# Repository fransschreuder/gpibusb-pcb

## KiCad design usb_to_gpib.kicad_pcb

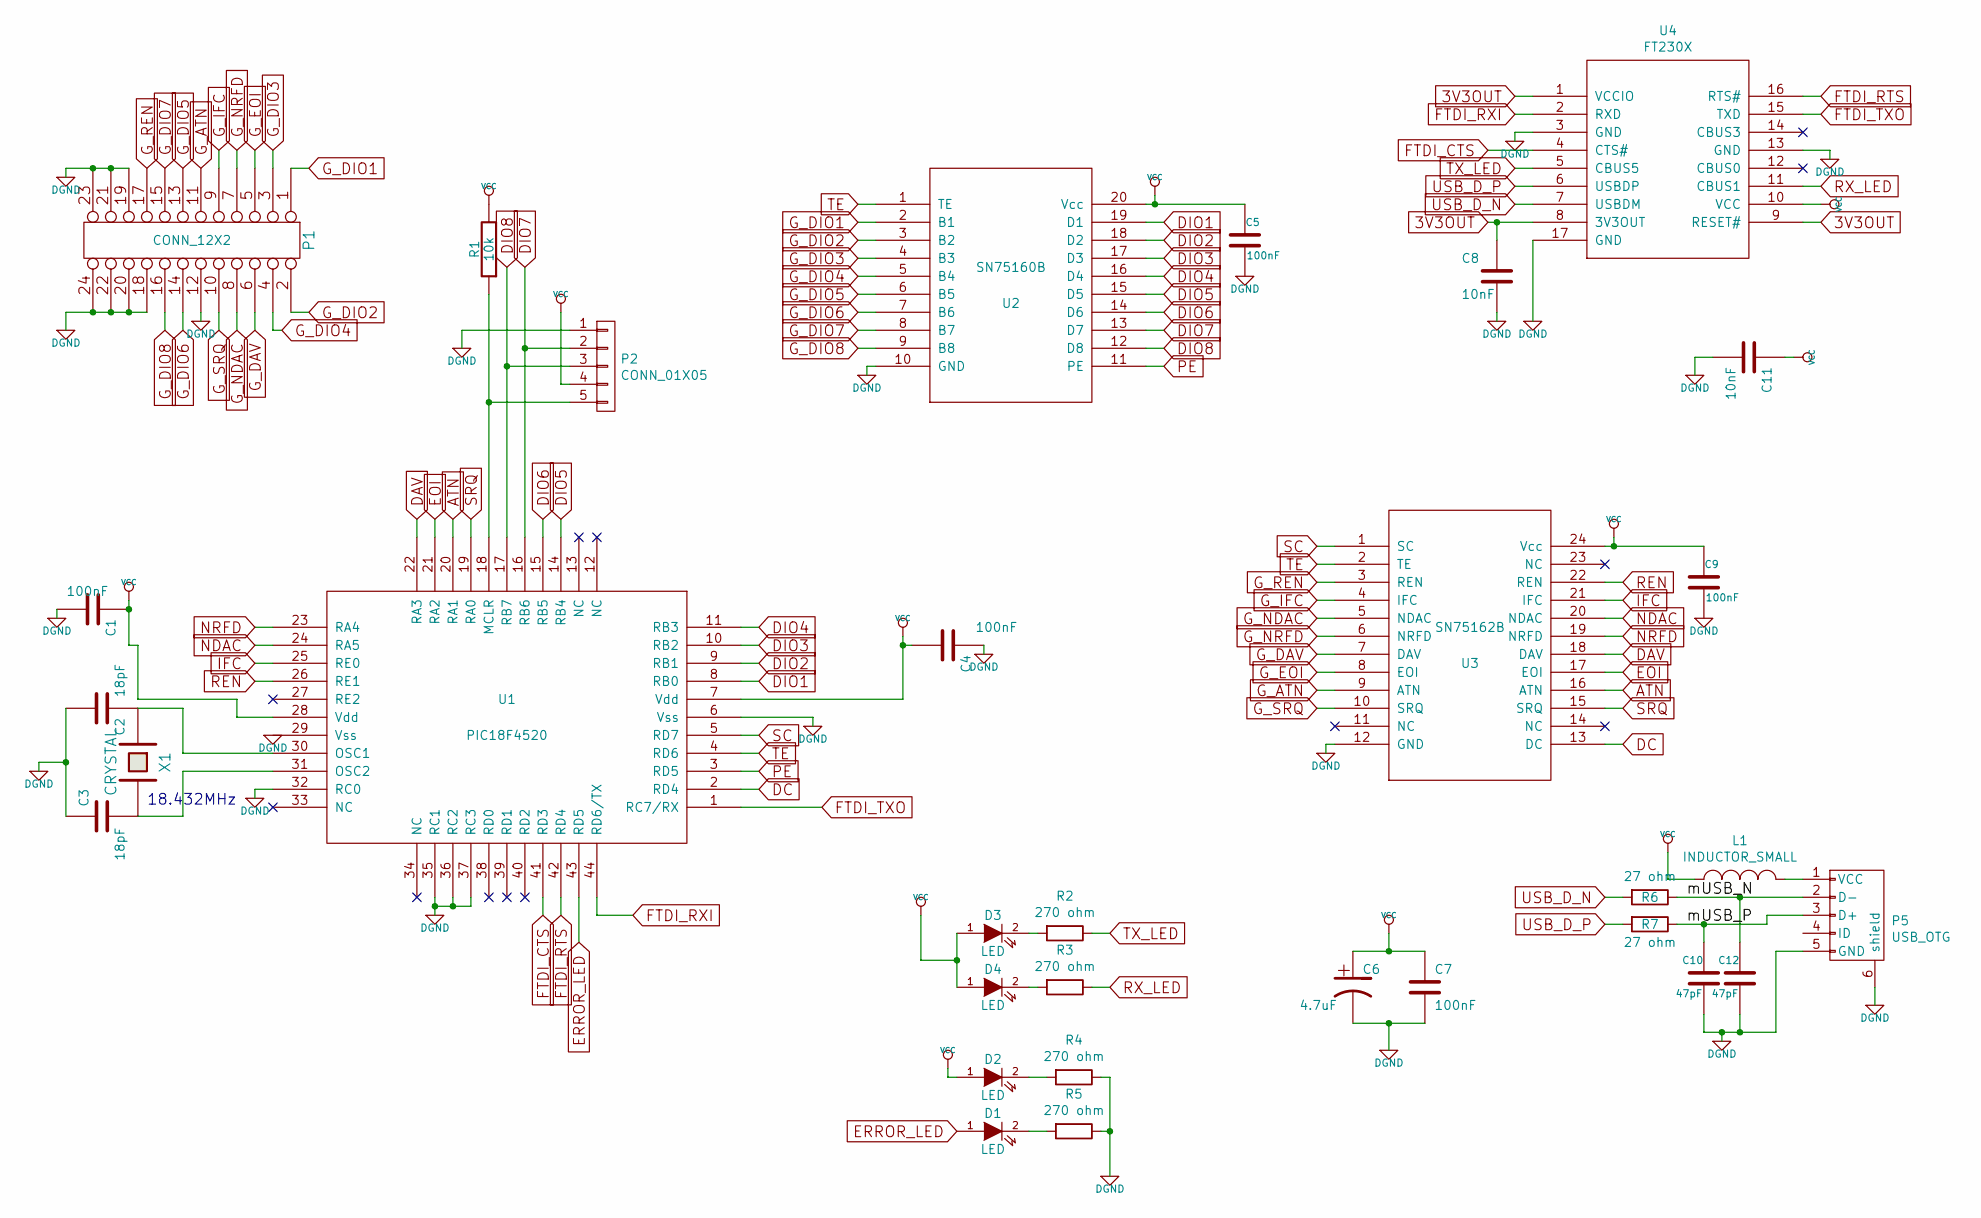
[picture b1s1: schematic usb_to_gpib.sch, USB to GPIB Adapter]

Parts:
C1, C4, C5, C7, C9: 100nF; C_0603
C2, C3: 18pF; C_0603
C6: 4.7uF; C_1210
C8, C11: 10nF; C_0603
C10, C12: 47pF; C_0603
D1, D2, D3, D4: LED; LED_0805
L1: INDUCTOR_SMALL; R_0603
P1: CONN_12X2; gpib_conn_male
P2: CONN_01X05; Pin_Header_Straight_1x05
P5: USB_OTG; USB_Mini-B
R1: 10k; R_0603
R2, R3, R4, R5: 270 ohm; R_0603
R6, R7: 27 ohm; R_0603
U1: PIC18F4520
U2: SN75160B; MODULE
U3: SN75162B; MODULE
U4: FT230X; MODULE
X1: CRYSTAL; ABM3

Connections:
3V3OUT: C8.1, U4.1 (VCCIO), U4.8 (3V3OUT), U4.9 (RESET#)
/mUSB_N: C12.1, P5.2 (D-), R6.1
/mUSB_P: C10.1, P5.3 (D+), R7.1
ATN: U1.20 (RA1), U3.16 (ATN)
DAV: U1.22 (RA3), U3.18 (DAV)
DC: U1.2 (RD4), U3.13 (DC)
DGND: C1.2, C2.2, C3.1, C4.1, C5.2, C6.2, C7.2, C8.2, C9.2, C10.2, C11.2, C12.2, P1.12, P1.18, P1.19, P1.20, P1.21, P1.22, P1.23, P1.24, P2.1, P5.5 (GND), P5.6 (shield), R4.1, R5.1, U1.6 (Vss), U1.29 (Vss), U1.32 (RC0), U1.35 (RC1), U1.36 (RC2), U1.37 (RC3), U2.10 (GND), U3.12 (GND), U4.3 (GND), U4.13 (GND), U4.17 (GND)
DIO1: U1.8 (RB0), U2.19 (D1)
DIO2: U1.9 (RB1), U2.18 (D2)
DIO3: U1.10 (RB2), U2.17 (D3)
DIO4: U1.11 (RB3), U2.16 (D4)
DIO5: U1.14 (RB4), U2.15 (D5)
DIO6: U1.15 (RB5), U2.14 (D6)
DIO7: P2.2, U1.16 (RB6), U2.13 (D7)
DIO8: P2.3, U1.17 (RB7), U2.12 (D8)
EOI: U1.21 (RA2), U3.17 (EOI)
ERROR_LED: D1.1 (A), U1.43 (RD5)
FTDI_CTS: U1.41 (RD3), U4.4 (CTS#)
FTDI_RTS: U1.42 (RD4), U4.16 (RTS#)
FTDI_RXI: U1.44 (RD6/TX), U4.2 (RXD)
FTDI_TXO: U1.1 (RC7/RX), U4.15 (TXD)
G_ATN: P1.11, U3.9 (ATN)
G_DAV: P1.6, U3.7 (DAV)
G_DIO1: P1.1, U2.2 (B1)
G_DIO2: P1.2, U2.3 (B2)
G_DIO3: P1.3, U2.4 (B3)
G_DIO4: P1.4, U2.5 (B4)
G_DIO5: P1.13, U2.6 (B5)
G_DIO6: P1.14, U2.7 (B6)
G_DIO7: P1.15, U2.8 (B7)
G_DIO8: P1.16, U2.9 (B8)
G_EOI: P1.5, U3.8 (EOI)
G_IFC: P1.9, U3.4 (IFC)
G_NDAC: P1.8, U3.5 (NDAC)
G_NRFD: P1.7, U3.6 (NRFD)
G_REN: P1.17, U3.3 (REN)
G_SRQ: P1.10, U3.10 (SRQ)
IFC: U1.25 (RE0), U3.21 (IFC)
NDAC: U1.24 (RA5), U3.20 (NDAC)
NRFD: U1.23 (RA4), U3.19 (NRFD)
unnamed: C2.1, U1.30 (OSC1), X1.1
unnamed: C3.2, U1.31 (OSC2), X1.2
unnamed: D1.2 (K), R5.2
unnamed: D2.2 (K), R4.2
unnamed: D3.2 (K), R2.2
unnamed: D4.2 (K), R3.2
unnamed: L1.2, P5.1 (VCC)
unnamed: P2.5, R1.1, U1.18 (MCLR)
PE: U1.3 (RD5), U2.11 (PE)
REN: U1.26 (RE1), U3.22 (REN)
RX_LED: R3.1, U4.11 (CBUS1)
SC: U1.5 (RD7), U3.1 (SC)
SRQ: U1.19 (RA0), U3.15 (SRQ)
TE: U1.4 (RD6), U2.1 (TE), U3.2 (TE)
TX_LED: R2.1, U4.5 (CBUS5)
USB_D_N: R6.2, U4.7 (USBDM)
USB_D_P: R7.2, U4.6 (USBDP)
VCC: C1.1, C4.2, C5.1, C6.1, C7.1, C9.1, C11.1, D2.1 (A), D3.1 (A), D4.1 (A), L1.1, P2.4, R1.2, U1.7 (Vdd), U1.28 (Vdd), U2.20 (Vcc), U3.24 (Vcc), U4.10 (VCC)

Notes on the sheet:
18.432MHz

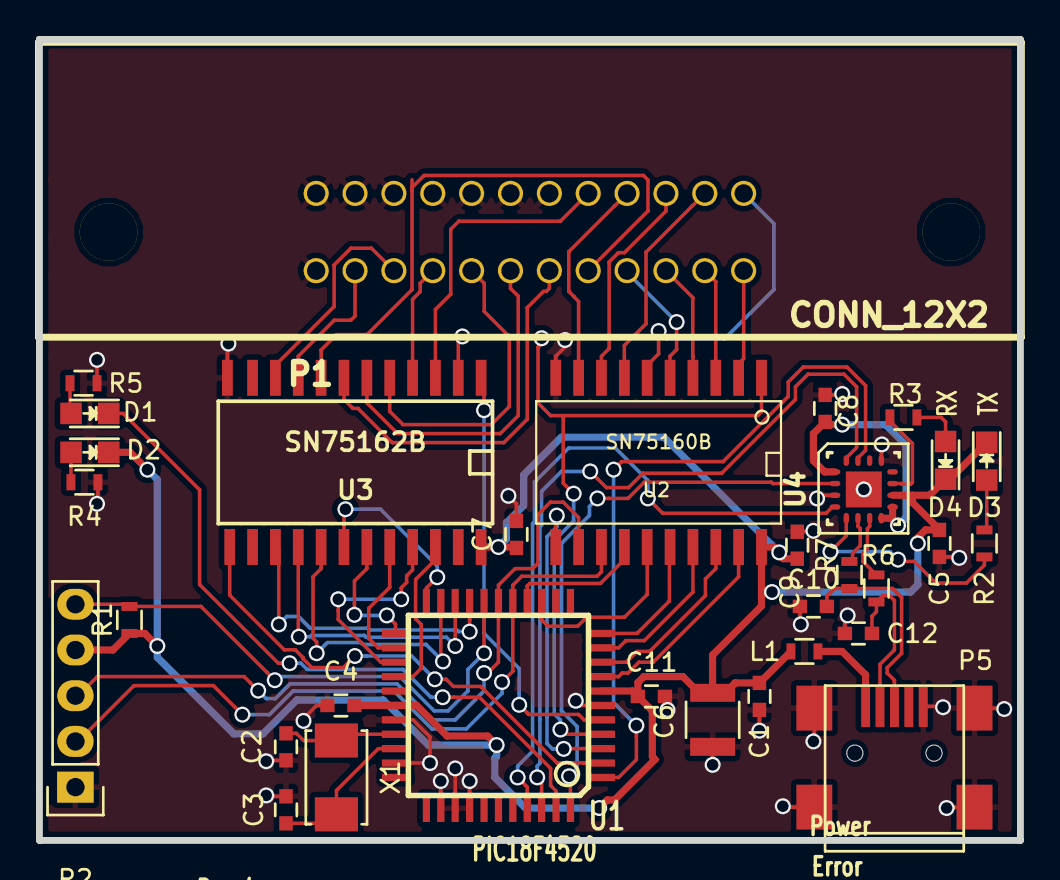
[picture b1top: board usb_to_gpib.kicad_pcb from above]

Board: 2 copper layers, 54.5 x 44.5 mm, 32 parts (0 on the bottom side), 58 nets.

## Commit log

2016-09-19 Some modifications: * removed exotic dual resistors * added usbpicprog compatible isp header * smaller board * usb mini connector
2016-09-19 renamed edge cuts to .gko

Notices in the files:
usb_to_gpib.kicad_pcb:
Released under Creative Commons
Attribution-ShareAlike 3.0 License
